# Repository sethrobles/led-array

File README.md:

# LED Array (32×32 STM32-Driven Matrix)

This repository contains the **hardware design and firmware** for a custom **32×32 LED matrix PCB** designed in **KiCad** and driven by an **STM32 microcontroller**.

The project was built both as a learning exercise in multi-layer PCB design and as a functional, firmware-controlled LED display.

🔗 **Project blog / design log:**
https://sethrobles.github.io/blogs/led-array/

---

## Project Overview

The LED array is implemented as a multiplexed matrix driven by shift registers and MOSFETs, with all timing and animation handled in firmware.

### Hardware Features

- **32×32 LED matrix** (1,032 LEDs total)
- **16× 74HC595 shift registers** for serial-to-parallel expansion
- **8× N-channel MOSFETs** for row/column current switching
- **STM32 microcontroller** for scanning, timing, and animation logic
- **On-board buck converter** for efficient 3.3 V regulation
- **4-layer PCB** designed and routed in KiCad
- **Hierarchical schematics** to support scalable layout and reuse

## Schematic Structure

The board uses an **on-board switching buck converter (TPS54331DR)** to step a ~5 V input down to 3.3V for the STM32 and logic circuitry.

The design uses a hierarchical schematic organization to keep both the schematic and PCB layout manageable:

- **LED Row**: 8 LEDs tied to a single shift-register output
- **LED Module**: One shift register driving 64 LEDs
- **LED Group**: Four LED modules grouped for layout and logic convenience

In total:
- **16 shift registers**
- **1,032 LEDs**

---

## Firmware

Firmware is written using **STM32CubeIDE** and is responsible for:

- High-speed LED scanning
- Register shifting and latch control
- Multiplex timing
- Multiple animation modes (spirals, perimeter effects, hearts, text, etc.)
- Minimizing ghosting and partial illumination

Programming and debugging are currently done using **ST-Link**. A future revision may include a USB bootloader to eliminate the need for programming headers.

Firmware lives alongside the hardware files but is kept logically separate. It is divided into 3 .c files: main, led_array, and frames. Main is actually uploaded to the board, led_array includes the basic logic for programming a frame, and frames contains specific frames for the board that build the animations.

---

## Repository Structure

- `Firmware/` – STM32 firmware source (CubeIDE project)
- KiCad project files – schematics, PCB layout, and libraries
- Backup and fabrication-related artifacts (not required for normal use)

---

## Status

The board has been fabricated, assembled, powered, and tested:

- Buck converter output verified (~20 mV ripple observed)
- STM32 successfully flashed and running on hardware
- LED scanning and animations functional

---

## Motivation & Inspiration

This project was inspired by:
- Phil’s Lab STM32 PCB design tutorials
- Guidance and feedback from friends with PCB design experience

The full design process, decisions, mistakes, and lessons learned are documented on the project blog.

📖 **Read the full build log:**
https://sethrobles.github.io/blogs/led-array/

*Summary Written with ChatGPT

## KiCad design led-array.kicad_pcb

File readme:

# KiCad LED Array 🚧 (Work in Progress)

This project is a custom PCB built in **KiCad** that drives a 32×32 LED matrix using an **STM32 microcontroller**.

The design features:
- **8 NFETs** for row/column control
- **16 shift registers (74HC595)** for serial-to-parallel expansion
- A hierarchical schematic setup for scalability

### Inspiration
This project was inspired (and guided) by my friend [@floreacton](https://github.com/floreacton).

---

## Current Status
🚧 **In Progress**
This design is still being prototyped. Expect changes to both the schematic and PCB layout as I refine the design.

---

## Goals
- [ ] Finish schematic design and ERC checks
- [ ] Route PCB with proper 4-layer stackup
- [ ] Order prototype boards from JLCPCB
- [ ] Test LED scanning with STM32 firmware

---

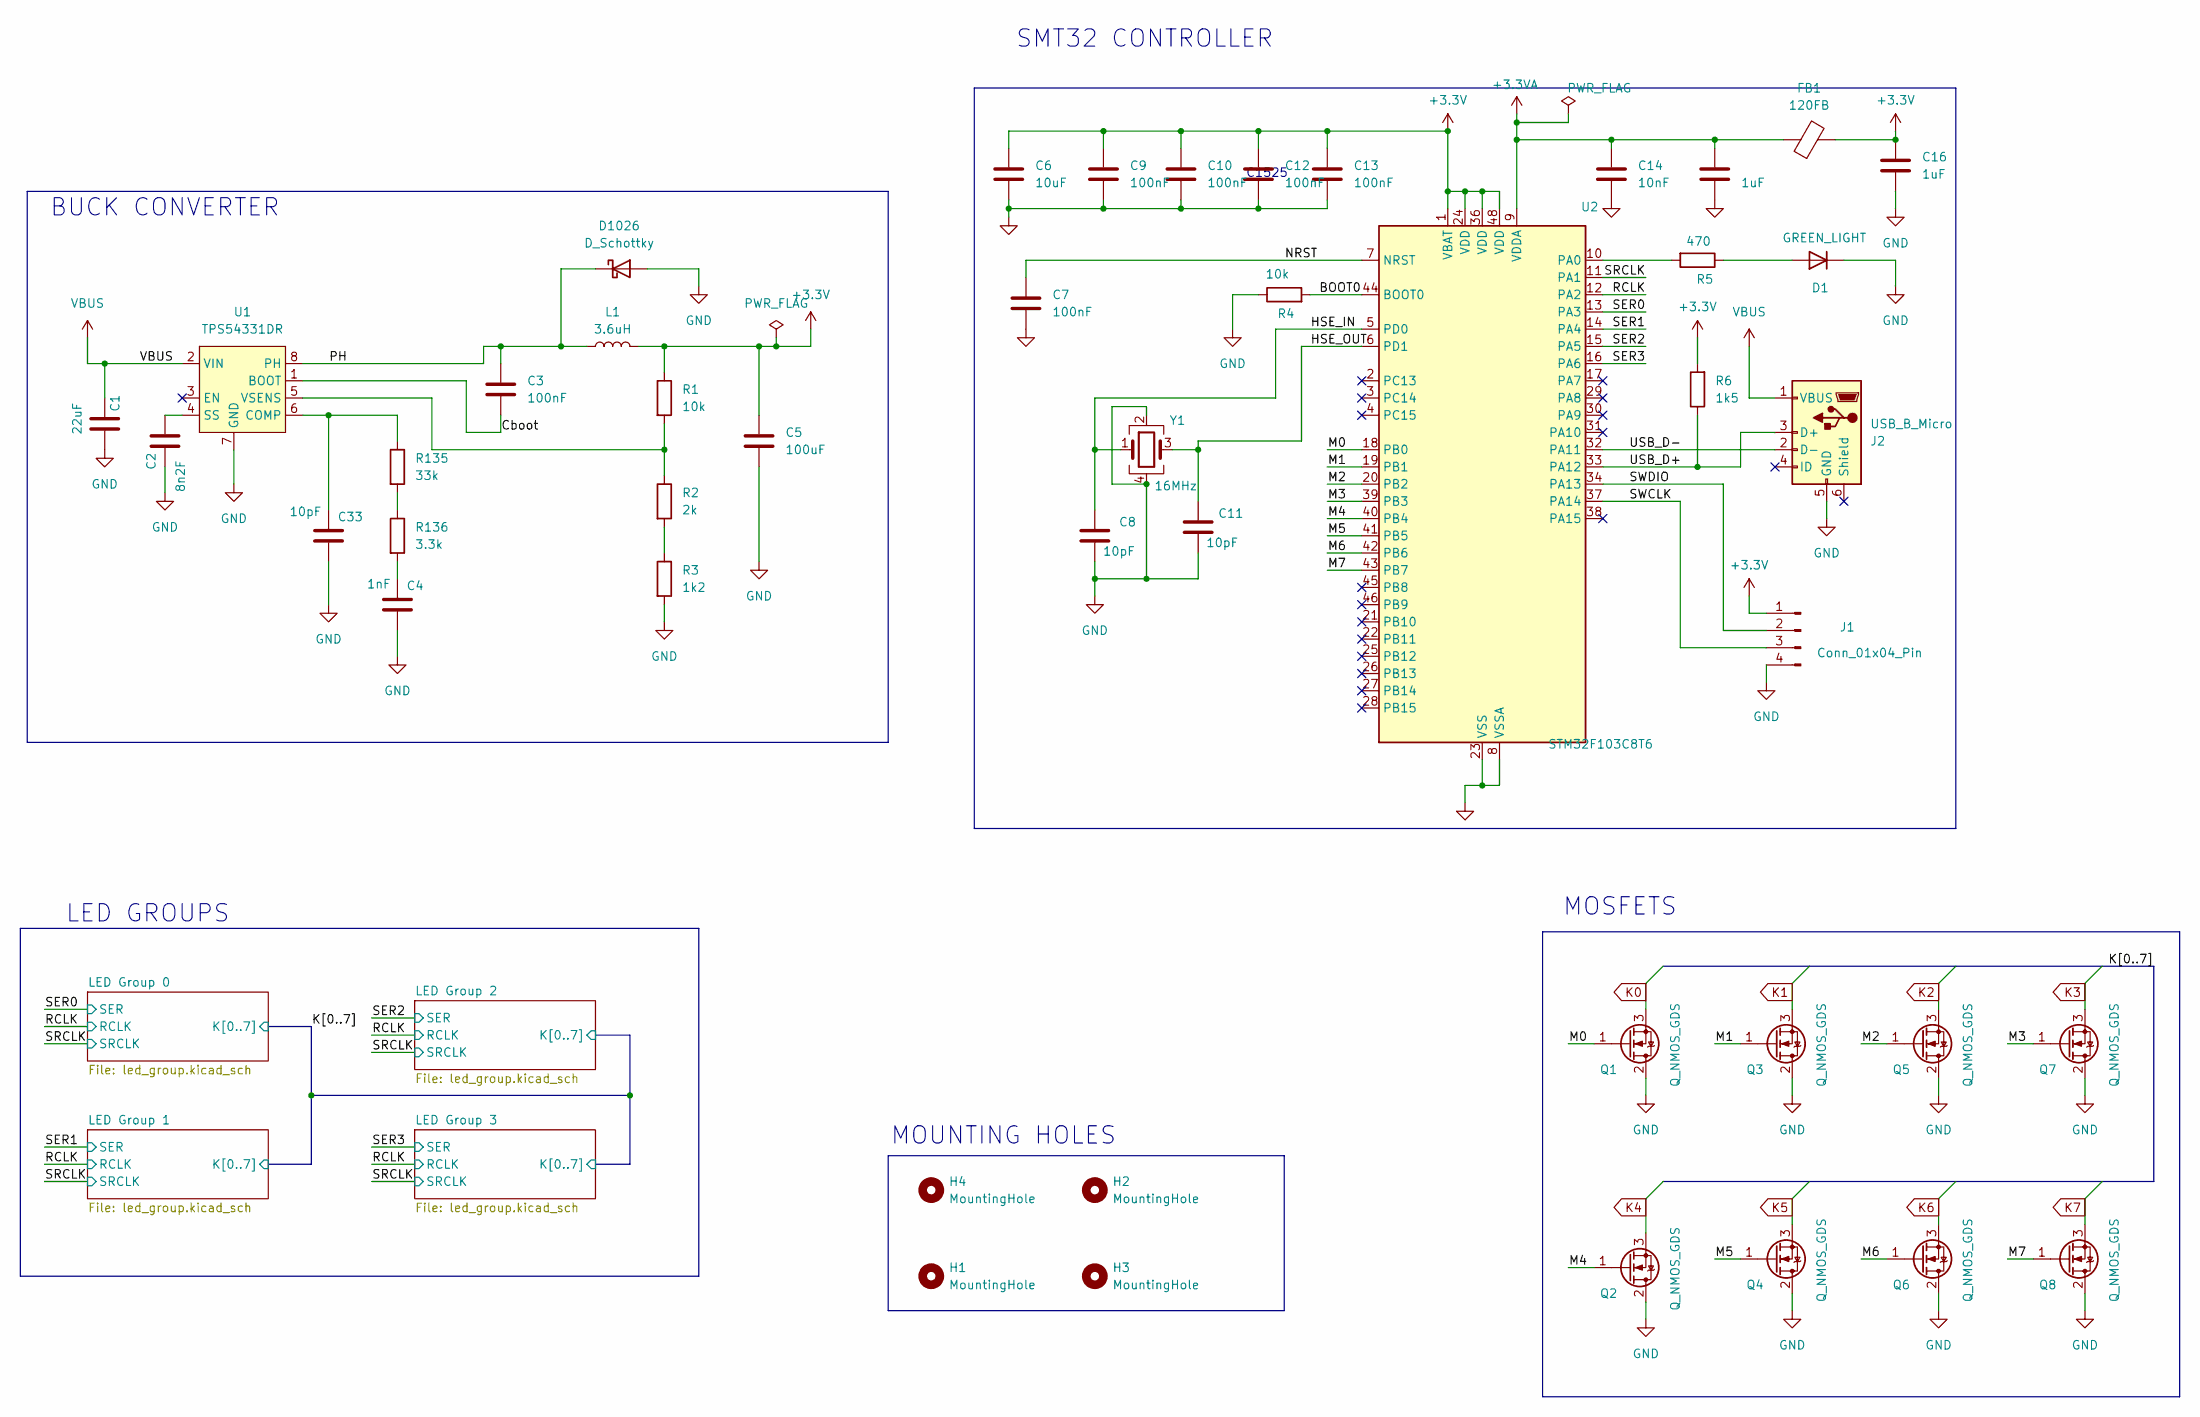
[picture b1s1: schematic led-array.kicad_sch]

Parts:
C1: 22uF; C_1206_3216Metric; LCSC C12891
C2: 8n2F; C_0603_1608Metric; LCSC C1322360
C3, C7, C9, C10, C12, C13: 100nF; C_0402_1005Metric; LCSC C1525
C4: 1nF; C_0402_1005Metric; LCSC C1523
C5: 100uF; C_1206_3216Metric; LCSC C15008
C6: 10uF; C_1206_3216Metric; LCSC C13585
C8, C11, C33: 10pF; C_0402_1005Metric; LCSC C32949
C14: 10nF; C_0603_1608Metric; LCSC C57112
C15, C16: 1uF; C_0603_1608Metric; LCSC C15849
D1: GREEN_LIGHT; LED_0805_2012Metric; LCSC C2297
D1026: D_Schottky; D_SMA; LCSC C14996
FB1: 120FB; L_0603_1608Metric; LCSC C14709
H1, H2, H3, H4: MountingHole; MountingHole_3.2mm_M3
J1: Conn_01x04_Pin; PinHeader_1x04_P2.54mm_Vertical; LCSC C5116483
J2: USB_B_Micro; USB_Micro-B_Molex-105017-0001; LCSC C136000
L1: 3.6uH; L_Bourns-SRN8040_8x8.15mm; LCSC C6496151
Q1, Q2, Q3, Q4, Q5, Q6, Q7, Q8: Q_NMOS_GDS; SOT-23; LCSC C8545
R1, R4: 10k; R_0805_2012Metric; LCSC C17414
R2: 2k; R_0402_1005Metric; LCSC C4109
R3: 1k2; R_0603_1608Metric; LCSC C22765
R5: 470; R_0402_1005Metric; LCSC C25117
R6: 1k5; R_0603_1608Metric; LCSC C22843
R135: 33k; R_0402_1005Metric; LCSC C25779
R136: 3.3k; R_0402_1005Metric; LCSC C25890
U1: TPS54331DR; SOIC-8_3.9x4.9mm_P1.27mm; LCSC C9865
U2: STM32F103C8T6; LQFP-48_7x7mm_P0.5mm; LCSC C8734
Y1: 16MHz; Crystal_SMD_3225-4Pin_3.2x2.5mm; LCSC C9002

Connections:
+3.3V: C5.1, C6.1, C9.1, C10.1, C12.1, C13.1, C16.1, FB1.2, J1.1, L1.2, R1.1, R6.2, U2.1 (VBAT), U2.24 (VDD), U2.36 (VDD), U2.48 (VDD); also elsewhere on the board
+3.3VA: C14.1, C15.1, FB1.1, U2.9 (VDDA)
/BOOT0: R4.2, U2.44 (BOOT0)
/Cboot: C3.2, U1.1 (BOOT)
/HSE_IN: C8.2, U2.5 (PD0), Y1.1
/HSE_OUT: C11.2, U2.6 (PD1), Y1.3
/M0: Q1.1 (G), U2.18 (PB0)
/M1: Q3.1 (G), U2.19 (PB1)
/M2: Q5.1 (G), U2.20 (PB2)
/M3: Q7.1 (G), U2.39 (PB3)
/M4: Q2.1 (G), U2.40 (PB4)
/M5: Q4.1 (G), U2.41 (PB5)
/M6: Q6.1 (G), U2.42 (PB6)
/M7: Q8.1 (G), U2.43 (PB7)
/NRST: C7.1, U2.7 (NRST)
/PH: C3.1, D1026.1 (K), L1.1, U1.8 (PH)
/RCLK: U2.12 (PA2); also elsewhere on the board
/SER0: U2.13 (PA3); also elsewhere on the board
/SER1: U2.14 (PA4); also elsewhere on the board
/SER2: U2.15 (PA5); also elsewhere on the board
/SER3: U2.16 (PA6); also elsewhere on the board
/SRCLK: U2.11 (PA1); also elsewhere on the board
/SWCLK: J1.3, U2.37 (PA14)
/SWDIO: J1.2, U2.34 (PA13)
/USB_D+: J2.3 (D+), R6.1, U2.33 (PA12)
/USB_D-: J2.2 (D-), U2.32 (PA11)
GND: C1.2, C2.2, C4.2, C5.2, C6.2, C7.2, C8.1, C9.2, C10.2, C11.1, C12.2, C13.2, C14.2, C15.2, C16.2, C33.2, D1.1 (K), D1026.2 (A), J1.4, J2.5 (GND), Q1.2 (D), Q2.2 (D), Q3.2 (D), Q4.2 (D), Q5.2 (D), Q6.2 (D), Q7.2 (D), Q8.2 (D), R3.2, R4.1, U1.7 (GND), U2.8 (VSSA), U2.23 (VSS), U2.35 (VSS), U2.47 (VSS), Y1.2, Y1.4; also elsewhere on the board
K0: Q1.3 (S); also elsewhere on the board
K1: Q3.3 (S); also elsewhere on the board
K2: Q5.3 (S); also elsewhere on the board
K3: Q7.3 (S); also elsewhere on the board
K4: Q2.3 (S); also elsewhere on the board
K5: Q4.3 (S); also elsewhere on the board
K6: Q6.3 (S); also elsewhere on the board
K7: Q8.3 (S); also elsewhere on the board
unnamed: C4.1, R136.2
unnamed: D1.2 (A), R5.1
unnamed: R2.2, R3.1
unnamed: R135.2, R136.1
unnamed: C33.1, R135.1, U1.6 (COMP)
unnamed: C2.1, U1.4 (SS)
unnamed: R1.2, R2.1, U1.5 (VSENS)
unnamed: R5.2, U2.10 (PA0)
VBUS: C1.1, J2.1 (VBUS), U1.2 (VIN)

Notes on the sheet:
SMT32 CONTROLLER
BUCK CONVERTER
MOUNTING HOLES
C1525
LED GROUPS
MOSFETS

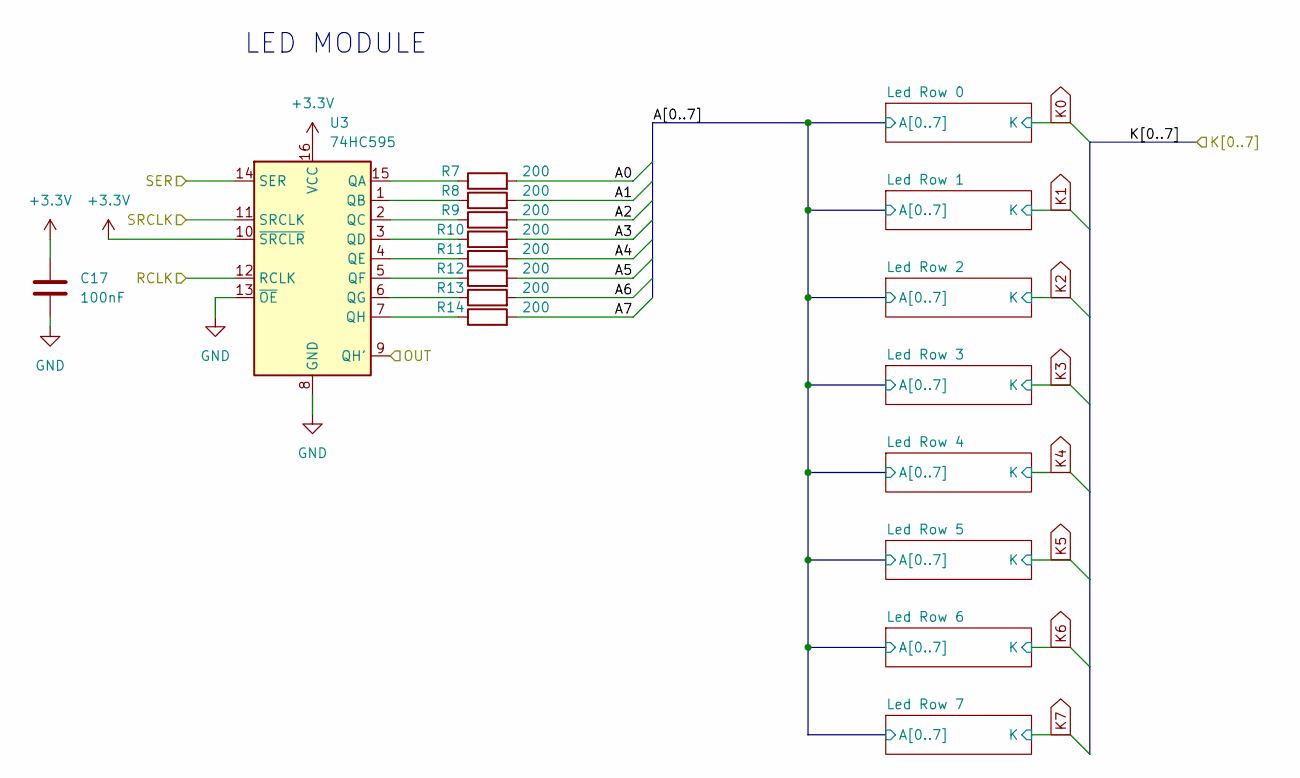
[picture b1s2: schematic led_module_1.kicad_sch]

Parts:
C17: 100nF; C_0402_1005Metric; LCSC C1525
R7, R8, R9, R10, R11, R12, R13, R14: 200; R_0402_1005Metric; LCSC C25087
U3: 74HC595; SOIC-16_3.9x9.9mm_P1.27mm; LCSC C5947

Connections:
+3.3V: C17.1, U3.10 (~SRCLR), U3.16 (VCC); also elsewhere on the board
/LED Group 0/Led Module 1/A0: R7.2; also elsewhere on the board
/LED Group 0/Led Module 1/A1: R8.2; also elsewhere on the board
/LED Group 0/Led Module 1/A2: R9.2; also elsewhere on the board
/LED Group 0/Led Module 1/A3: R10.2; also elsewhere on the board
/LED Group 0/Led Module 1/A4: R11.2; also elsewhere on the board
/LED Group 0/Led Module 1/A5: R12.2; also elsewhere on the board
/LED Group 0/Led Module 1/A6: R13.2; also elsewhere on the board
/LED Group 0/Led Module 1/A7: R14.2; also elsewhere on the board
/LED Group 0/Led Module 1/OUT: U3.9 (QH'); also elsewhere on the board
/RCLK: U3.12 (RCLK); also elsewhere on the board
/SER0: U3.14 (SER); also elsewhere on the board
/SRCLK: U3.11 (SRCLK); also elsewhere on the board
GND: C17.2, U3.8 (GND), U3.13 (~OE); also elsewhere on the board
unnamed: R7.1, U3.15 (QA)
unnamed: R8.1, U3.1 (QB)
unnamed: R9.1, U3.2 (QC)
unnamed: R10.1, U3.3 (QD)
unnamed: R11.1, U3.4 (QE)
unnamed: R12.1, U3.5 (QF)
unnamed: R13.1, U3.6 (QG)
unnamed: R14.1, U3.7 (QH)

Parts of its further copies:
C18, C19, C20, C21, C22, C23, C24, C25, C26, C27, C28, C29, C30, C31, C32: 100nF; C_0402_1005Metric; LCSC C1525
R15, R16, R17, R18, R19, R20, R21, R22, R23, R24, R25, R26, R27, R28, R29, R30, R31, R32, R33, R34, R35, R36, R37, R38, R39, R40, R41, R42, R43, R44, R45, R46, R47, R48, R49, R50, R51, R52, R53, R54, R55, R56, R57, R58, R59, R60, R61, R62, R63, R64, R65, R66, R67, R68, R69, R70, R71, R72, R73, R74, R75, R76, R77, R78, R79, R80, R81, R82, R83, R84, R85, R86, R87, R88, R89, R90, R91, R92, R93, R94, R95, R96, R97, R98, R99, R100, R101, R102, R103, R104, R105, R106, R107, R108, R109, R110, R111, R112, R113, R114, R115, R116, R117, R118, R119, R120, R121, R122, R123, R124, R125, R126, R127, R128, R129, R130, R131, R132, R133, R134: 200; R_0402_1005Metric; LCSC C25087
U4, U5, U6, U7, U8, U9, U10, U11, U12, U13, U14, U15, U16, U17, U18: 74HC595; SOIC-16_3.9x9.9mm_P1.27mm; LCSC C5947

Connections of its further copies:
+3.3V: C18.1, C19.1, C20.1, C21.1, C22.1, C23.1, C24.1, C25.1, C26.1, C27.1, C28.1, C29.1, C30.1, C31.1, C32.1, U4.10 (~SRCLR), U4.16 (VCC), U5.10 (~SRCLR), U5.16 (VCC), U6.10 (~SRCLR), U6.16 (VCC), U7.10 (~SRCLR), U7.16 (VCC), U8.10 (~SRCLR), U8.16 (VCC), U9.10 (~SRCLR), U9.16 (VCC), U10.10 (~SRCLR), U10.16 (VCC), U11.10 (~SRCLR), U11.16 (VCC), U12.10 (~SRCLR), U12.16 (VCC), U13.10 (~SRCLR), U13.16 (VCC), U14.10 (~SRCLR), U14.16 (VCC), U15.10 (~SRCLR), U15.16 (VCC), U16.10 (~SRCLR), U16.16 (VCC), U17.10 (~SRCLR), U17.16 (VCC), U18.10 (~SRCLR), U18.16 (VCC); also elsewhere on the board
/LED Group 0/Led Module 1/OUT: U4.14 (SER); also elsewhere on the board
/LED Group 0/Led Module 2/A0: R15.2; also elsewhere on the board
/LED Group 0/Led Module 2/A1: R16.2; also elsewhere on the board
/LED Group 0/Led Module 2/A2: R17.2; also elsewhere on the board
/LED Group 0/Led Module 2/A3: R18.2; also elsewhere on the board
/LED Group 0/Led Module 2/A4: R19.2; also elsewhere on the board
/LED Group 0/Led Module 2/A5: R20.2; also elsewhere on the board
/LED Group 0/Led Module 2/A6: R21.2; also elsewhere on the board
/LED Group 0/Led Module 2/A7: R22.2; also elsewhere on the board
/LED Group 0/Led Module 2/OUT: U4.9 (QH'), U5.14 (SER)
/LED Group 0/Led Module 3/A0: R23.2; also elsewhere on the board
/LED Group 0/Led Module 3/A1: R24.2; also elsewhere on the board
/LED Group 0/Led Module 3/A2: R25.2; also elsewhere on the board
/LED Group 0/Led Module 3/A3: R26.2; also elsewhere on the board
/LED Group 0/Led Module 3/A4: R27.2; also elsewhere on the board
/LED Group 0/Led Module 3/A5: R28.2; also elsewhere on the board
/LED Group 0/Led Module 3/A6: R29.2; also elsewhere on the board
/LED Group 0/Led Module 3/A7: R30.2; also elsewhere on the board
/LED Group 0/Led Module 3/OUT: U5.9 (QH'), U6.14 (SER)
/LED Group 0/Led Module 4/A0: R31.2; also elsewhere on the board
/LED Group 0/Led Module 4/A1: R32.2; also elsewhere on the board
/LED Group 0/Led Module 4/A2: R33.2; also elsewhere on the board
/LED Group 0/Led Module 4/A3: R34.2; also elsewhere on the board
/LED Group 0/Led Module 4/A4: R35.2; also elsewhere on the board
/LED Group 0/Led Module 4/A5: R36.2; also elsewhere on the board
/LED Group 0/Led Module 4/A6: R37.2; also elsewhere on the board
/LED Group 0/Led Module 4/A7: R38.2; also elsewhere on the board
/LED Group 0/Led Module 4/OUT: U6.9 (QH')
/LED Group 1/Led Module 1/A0: R47.2; also elsewhere on the board
/LED Group 1/Led Module 1/A1: R48.2; also elsewhere on the board
/LED Group 1/Led Module 1/A2: R49.2; also elsewhere on the board
/LED Group 1/Led Module 1/A3: R50.2; also elsewhere on the board
/LED Group 1/Led Module 1/A4: R51.2; also elsewhere on the board
/LED Group 1/Led Module 1/A5: R52.2; also elsewhere on the board
/LED Group 1/Led Module 1/A6: R53.2; also elsewhere on the board
/LED Group 1/Led Module 1/A7: R54.2; also elsewhere on the board
/LED Group 1/Led Module 1/OUT: U7.14 (SER), U8.9 (QH')
/LED Group 1/Led Module 2/A0: R39.2; also elsewhere on the board
/LED Group 1/Led Module 2/A1: R40.2; also elsewhere on the board
/LED Group 1/Led Module 2/A2: R41.2; also elsewhere on the board
/LED Group 1/Led Module 2/A3: R42.2; also elsewhere on the board
/LED Group 1/Led Module 2/A4: R43.2; also elsewhere on the board
/LED Group 1/Led Module 2/A5: R44.2; also elsewhere on the board
/LED Group 1/Led Module 2/A6: R45.2; also elsewhere on the board
/LED Group 1/Led Module 2/A7: R46.2; also elsewhere on the board
/LED Group 1/Led Module 2/OUT: U7.9 (QH'), U9.14 (SER)
/LED Group 1/Led Module 3/A0: R55.2; also elsewhere on the board
/LED Group 1/Led Module 3/A1: R56.2; also elsewhere on the board
/LED Group 1/Led Module 3/A2: R57.2; also elsewhere on the board
/LED Group 1/Led Module 3/A3: R58.2; also elsewhere on the board
/LED Group 1/Led Module 3/A4: R59.2; also elsewhere on the board
/LED Group 1/Led Module 3/A5: R60.2; also elsewhere on the board
/LED Group 1/Led Module 3/A6: R61.2; also elsewhere on the board
/LED Group 1/Led Module 3/A7: R62.2; also elsewhere on the board
/LED Group 1/Led Module 3/OUT: U9.9 (QH'), U10.14 (SER)
/LED Group 1/Led Module 4/A0: R63.2; also elsewhere on the board
/LED Group 1/Led Module 4/A1: R64.2; also elsewhere on the board
/LED Group 1/Led Module 4/A2: R65.2; also elsewhere on the board
/LED Group 1/Led Module 4/A3: R66.2; also elsewhere on the board
/LED Group 1/Led Module 4/A4: R67.2; also elsewhere on the board
/LED Group 1/Led Module 4/A5: R68.2; also elsewhere on the board
/LED Group 1/Led Module 4/A6: R69.2; also elsewhere on the board
/LED Group 1/Led Module 4/A7: R70.2; also elsewhere on the board
/LED Group 1/Led Module 4/OUT: U10.9 (QH')
/LED Group 2/Led Module 1/A0: R79.2; also elsewhere on the board
/LED Group 2/Led Module 1/A1: R80.2; also elsewhere on the board
/LED Group 2/Led Module 1/A2: R81.2; also elsewhere on the board
/LED Group 2/Led Module 1/A3: R82.2; also elsewhere on the board
/LED Group 2/Led Module 1/A4: R83.2; also elsewhere on the board
/LED Group 2/Led Module 1/A5: R84.2; also elsewhere on the board
/LED Group 2/Led Module 1/A6: R85.2; also elsewhere on the board
/LED Group 2/Led Module 1/A7: R86.2; also elsewhere on the board
/LED Group 2/Led Module 1/OUT: U11.14 (SER), U12.9 (QH')
/LED Group 2/Led Module 2/A0: R71.2; also elsewhere on the board
/LED Group 2/Led Module 2/A1: R72.2; also elsewhere on the board
/LED Group 2/Led Module 2/A2: R73.2; also elsewhere on the board
/LED Group 2/Led Module 2/A3: R74.2; also elsewhere on the board
/LED Group 2/Led Module 2/A4: R75.2; also elsewhere on the board
/LED Group 2/Led Module 2/A5: R76.2; also elsewhere on the board
/LED Group 2/Led Module 2/A6: R77.2; also elsewhere on the board
/LED Group 2/Led Module 2/A7: R78.2; also elsewhere on the board
/LED Group 2/Led Module 2/OUT: U11.9 (QH'), U13.14 (SER)
/LED Group 2/Led Module 3/A0: R87.2; also elsewhere on the board
/LED Group 2/Led Module 3/A1: R88.2; also elsewhere on the board
/LED Group 2/Led Module 3/A2: R89.2; also elsewhere on the board
/LED Group 2/Led Module 3/A3: R90.2; also elsewhere on the board
/LED Group 2/Led Module 3/A4: R91.2; also elsewhere on the board
/LED Group 2/Led Module 3/A5: R92.2; also elsewhere on the board
/LED Group 2/Led Module 3/A6: R93.2; also elsewhere on the board
/LED Group 2/Led Module 3/A7: R94.2; also elsewhere on the board
/LED Group 2/Led Module 3/OUT: U13.9 (QH'), U14.14 (SER)
/LED Group 2/Led Module 4/A0: R95.2; also elsewhere on the board
/LED Group 2/Led Module 4/A1: R96.2; also elsewhere on the board
/LED Group 2/Led Module 4/A2: R97.2; also elsewhere on the board
/LED Group 2/Led Module 4/A3: R98.2; also elsewhere on the board
/LED Group 2/Led Module 4/A4: R99.2; also elsewhere on the board
/LED Group 2/Led Module 4/A5: R100.2; also elsewhere on the board
/LED Group 2/Led Module 4/A6: R101.2; also elsewhere on the board
/LED Group 2/Led Module 4/A7: R102.2; also elsewhere on the board
/LED Group 2/Led Module 4/OUT: U14.9 (QH')
/LED Group 3/Led Module 1/A0: R111.2; also elsewhere on the board
/LED Group 3/Led Module 1/A1: R112.2; also elsewhere on the board
/LED Group 3/Led Module 1/A2: R113.2; also elsewhere on the board
/LED Group 3/Led Module 1/A3: R114.2; also elsewhere on the board
/LED Group 3/Led Module 1/A4: R115.2; also elsewhere on the board
/LED Group 3/Led Module 1/A5: R116.2; also elsewhere on the board
/LED Group 3/Led Module 1/A6: R117.2; also elsewhere on the board
/LED Group 3/Led Module 1/A7: R118.2; also elsewhere on the board
/LED Group 3/Led Module 1/OUT: U15.14 (SER), U16.9 (QH')
/LED Group 3/Led Module 2/A0: R103.2; also elsewhere on the board
/LED Group 3/Led Module 2/A1: R104.2; also elsewhere on the board
/LED Group 3/Led Module 2/A2: R105.2; also elsewhere on the board
/LED Group 3/Led Module 2/A3: R106.2; also elsewhere on the board
/LED Group 3/Led Module 2/A4: R107.2; also elsewhere on the board
/LED Group 3/Led Module 2/A5: R108.2; also elsewhere on the board
/LED Group 3/Led Module 2/A6: R109.2; also elsewhere on the board
/LED Group 3/Led Module 2/A7: R110.2; also elsewhere on the board
/LED Group 3/Led Module 2/OUT: U15.9 (QH'), U17.14 (SER)
/LED Group 3/Led Module 3/A0: R119.2; also elsewhere on the board
/LED Group 3/Led Module 3/A1: R120.2; also elsewhere on the board
/LED Group 3/Led Module 3/A2: R121.2; also elsewhere on the board
/LED Group 3/Led Module 3/A3: R122.2; also elsewhere on the board
/LED Group 3/Led Module 3/A4: R123.2; also elsewhere on the board
/LED Group 3/Led Module 3/A5: R124.2; also elsewhere on the board
/LED Group 3/Led Module 3/A6: R125.2; also elsewhere on the board
/LED Group 3/Led Module 3/A7: R126.2; also elsewhere on the board
/LED Group 3/Led Module 3/OUT: U17.9 (QH'), U18.14 (SER)
/LED Group 3/Led Module 4/A0: R127.2; also elsewhere on the board
/LED Group 3/Led Module 4/A1: R128.2; also elsewhere on the board
/LED Group 3/Led Module 4/A2: R129.2; also elsewhere on the board
/LED Group 3/Led Module 4/A3: R130.2; also elsewhere on the board
/LED Group 3/Led Module 4/A4: R131.2; also elsewhere on the board
/LED Group 3/Led Module 4/A5: R132.2; also elsewhere on the board
/LED Group 3/Led Module 4/A6: R133.2; also elsewhere on the board
/LED Group 3/Led Module 4/A7: R134.2; also elsewhere on the board
/LED Group 3/Led Module 4/OUT: U18.9 (QH')
/RCLK: U4.12 (RCLK), U5.12 (RCLK), U6.12 (RCLK), U7.12 (RCLK), U8.12 (RCLK), U9.12 (RCLK), U10.12 (RCLK), U11.12 (RCLK), U12.12 (RCLK), U13.12 (RCLK), U14.12 (RCLK), U15.12 (RCLK), U16.12 (RCLK), U17.12 (RCLK), U18.12 (RCLK); also elsewhere on the board
/SER1: U8.14 (SER); also elsewhere on the board
/SER2: U12.14 (SER); also elsewhere on the board
/SER3: U16.14 (SER); also elsewhere on the board
/SRCLK: U4.11 (SRCLK), U5.11 (SRCLK), U6.11 (SRCLK), U7.11 (SRCLK), U8.11 (SRCLK), U9.11 (SRCLK), U10.11 (SRCLK), U11.11 (SRCLK), U12.11 (SRCLK), U13.11 (SRCLK), U14.11 (SRCLK), U15.11 (SRCLK), U16.11 (SRCLK), U17.11 (SRCLK), U18.11 (SRCLK); also elsewhere on the board
GND: C18.2, C19.2, C20.2, C21.2, C22.2, C23.2, C24.2, C25.2, C26.2, C27.2, C28.2, C29.2, C30.2, C31.2, C32.2, U4.8 (GND), U4.13 (~OE), U5.8 (GND), U5.13 (~OE), U6.8 (GND), U6.13 (~OE), U7.8 (GND), U7.13 (~OE), U8.8 (GND), U8.13 (~OE), U9.8 (GND), U9.13 (~OE), U10.8 (GND), U10.13 (~OE), U11.8 (GND), U11.13 (~OE), U12.8 (GND), U12.13 (~OE), U13.8 (GND), U13.13 (~OE), U14.8 (GND), U14.13 (~OE), U15.8 (GND), U15.13 (~OE), U16.8 (GND), U16.13 (~OE), U17.8 (GND), U17.13 (~OE), U18.8 (GND), U18.13 (~OE); also elsewhere on the board
unnamed: R15.1, U4.15 (QA)
unnamed: R16.1, U4.1 (QB)
unnamed: R17.1, U4.2 (QC)
unnamed: R18.1, U4.3 (QD)
unnamed: R19.1, U4.4 (QE)
unnamed: R20.1, U4.5 (QF)
unnamed: R21.1, U4.6 (QG)
unnamed: R22.1, U4.7 (QH)
unnamed: R23.1, U5.15 (QA)
unnamed: R24.1, U5.1 (QB)
unnamed: R25.1, U5.2 (QC)
unnamed: R26.1, U5.3 (QD)
unnamed: R27.1, U5.4 (QE)
unnamed: R28.1, U5.5 (QF)
unnamed: R29.1, U5.6 (QG)
unnamed: R30.1, U5.7 (QH)
unnamed: R31.1, U6.15 (QA)
unnamed: R32.1, U6.1 (QB)
unnamed: R33.1, U6.2 (QC)
unnamed: R34.1, U6.3 (QD)
unnamed: R35.1, U6.4 (QE)
unnamed: R36.1, U6.5 (QF)
unnamed: R37.1, U6.6 (QG)
unnamed: R38.1, U6.7 (QH)
unnamed: R39.1, U7.15 (QA)
unnamed: R40.1, U7.1 (QB)
unnamed: R41.1, U7.2 (QC)
unnamed: R42.1, U7.3 (QD)
unnamed: R43.1, U7.4 (QE)
unnamed: R44.1, U7.5 (QF)
unnamed: R45.1, U7.6 (QG)
unnamed: R46.1, U7.7 (QH)
unnamed: R47.1, U8.15 (QA)
unnamed: R48.1, U8.1 (QB)
unnamed: R49.1, U8.2 (QC)
unnamed: R50.1, U8.3 (QD)
unnamed: R51.1, U8.4 (QE)
unnamed: R52.1, U8.5 (QF)
unnamed: R53.1, U8.6 (QG)
unnamed: R54.1, U8.7 (QH)
unnamed: R55.1, U9.15 (QA)
unnamed: R56.1, U9.1 (QB)
unnamed: R57.1, U9.2 (QC)
unnamed: R58.1, U9.3 (QD)
unnamed: R59.1, U9.4 (QE)
unnamed: R60.1, U9.5 (QF)
unnamed: R61.1, U9.6 (QG)
unnamed: R62.1, U9.7 (QH)
unnamed: R63.1, U10.15 (QA)
unnamed: R64.1, U10.1 (QB)
unnamed: R65.1, U10.2 (QC)
unnamed: R66.1, U10.3 (QD)
unnamed: R67.1, U10.4 (QE)
unnamed: R68.1, U10.5 (QF)
unnamed: R69.1, U10.6 (QG)
unnamed: R70.1, U10.7 (QH)
unnamed: R71.1, U11.15 (QA)
unnamed: R72.1, U11.1 (QB)
unnamed: R73.1, U11.2 (QC)
unnamed: R74.1, U11.3 (QD)
unnamed: R75.1, U11.4 (QE)
unnamed: R76.1, U11.5 (QF)
unnamed: R77.1, U11.6 (QG)
unnamed: R78.1, U11.7 (QH)
unnamed: R79.1, U12.15 (QA)
unnamed: R80.1, U12.1 (QB)
unnamed: R81.1, U12.2 (QC)
unnamed: R82.1, U12.3 (QD)
unnamed: R83.1, U12.4 (QE)
unnamed: R84.1, U12.5 (QF)
unnamed: R85.1, U12.6 (QG)
unnamed: R86.1, U12.7 (QH)
unnamed: R87.1, U13.15 (QA)
unnamed: R88.1, U13.1 (QB)
unnamed: R89.1, U13.2 (QC)
unnamed: R90.1, U13.3 (QD)
unnamed: R91.1, U13.4 (QE)
unnamed: R92.1, U13.5 (QF)
unnamed: R93.1, U13.6 (QG)
unnamed: R94.1, U13.7 (QH)
unnamed: R95.1, U14.15 (QA)
unnamed: R96.1, U14.1 (QB)
unnamed: R97.1, U14.2 (QC)
unnamed: R98.1, U14.3 (QD)
unnamed: R99.1, U14.4 (QE)
unnamed: R100.1, U14.5 (QF)
unnamed: R101.1, U14.6 (QG)
unnamed: R102.1, U14.7 (QH)
unnamed: R103.1, U15.15 (QA)
unnamed: R104.1, U15.1 (QB)
unnamed: R105.1, U15.2 (QC)
unnamed: R106.1, U15.3 (QD)
unnamed: R107.1, U15.4 (QE)
unnamed: R108.1, U15.5 (QF)
unnamed: R109.1, U15.6 (QG)
unnamed: R110.1, U15.7 (QH)
unnamed: R111.1, U16.15 (QA)
unnamed: R112.1, U16.1 (QB)
unnamed: R113.1, U16.2 (QC)
unnamed: R114.1, U16.3 (QD)
unnamed: R115.1, U16.4 (QE)
unnamed: R116.1, U16.5 (QF)
unnamed: R117.1, U16.6 (QG)
unnamed: R118.1, U16.7 (QH)
unnamed: R119.1, U17.15 (QA)
unnamed: R120.1, U17.1 (QB)
unnamed: R121.1, U17.2 (QC)
unnamed: R122.1, U17.3 (QD)
unnamed: R123.1, U17.4 (QE)
unnamed: R124.1, U17.5 (QF)
unnamed: R125.1, U17.6 (QG)
unnamed: R126.1, U17.7 (QH)
unnamed: R127.1, U18.15 (QA)
unnamed: R128.1, U18.1 (QB)
unnamed: R129.1, U18.2 (QC)
unnamed: R130.1, U18.3 (QD)
unnamed: R131.1, U18.4 (QE)
unnamed: R132.1, U18.5 (QF)
unnamed: R133.1, U18.6 (QG)
unnamed: R134.1, U18.7 (QH)

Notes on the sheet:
LED MODULE
